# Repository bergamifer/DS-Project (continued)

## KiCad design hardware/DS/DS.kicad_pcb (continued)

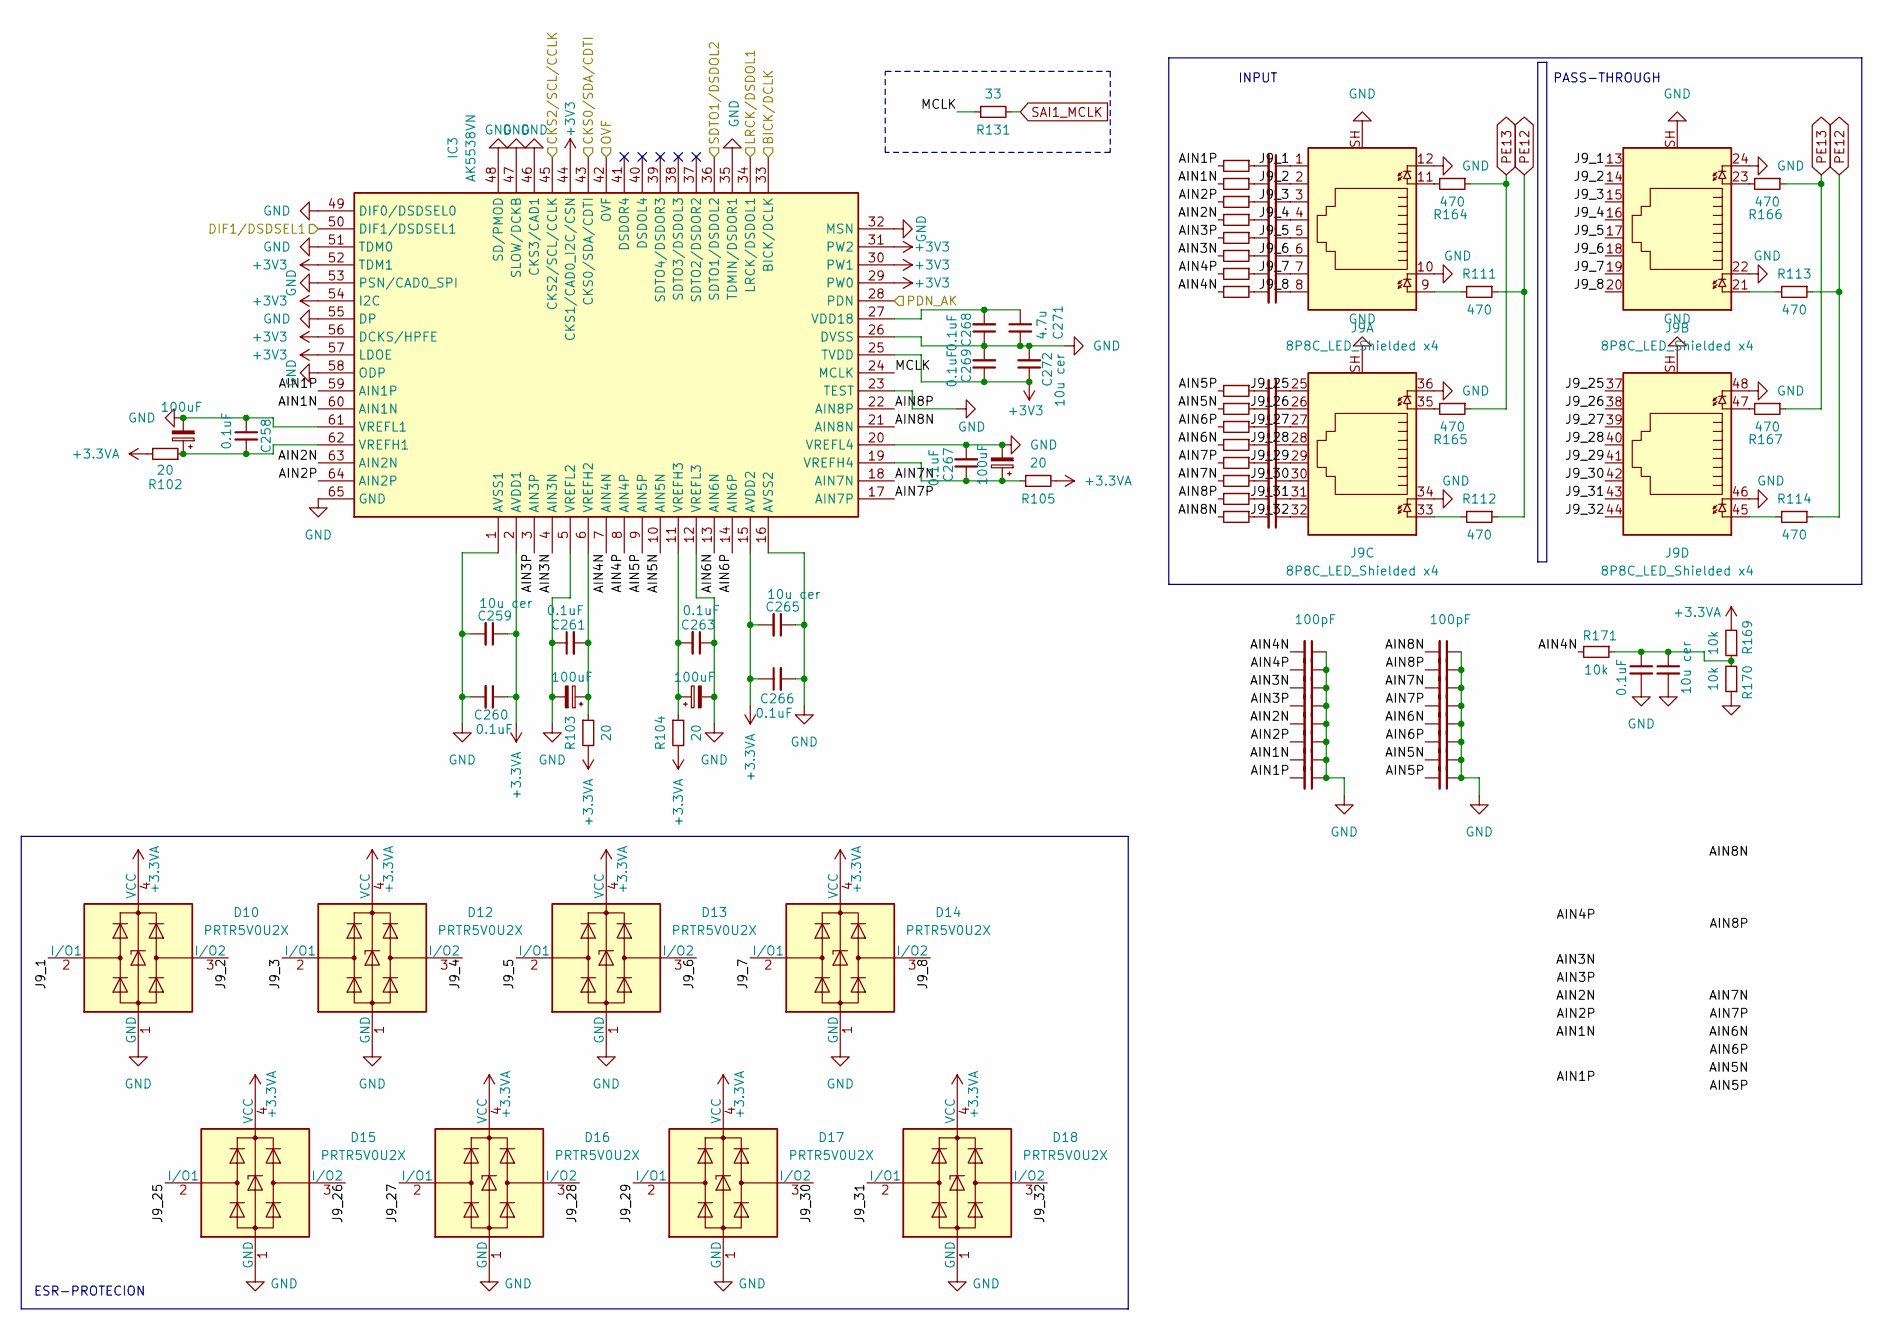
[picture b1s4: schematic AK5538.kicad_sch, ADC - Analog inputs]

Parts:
C58, C258, C260, C261, C263, C266, C267, C268, C269: 0.1uF; C_0402_1005Metric; Mouser part 581-KGM15BR71E104KT
C62, C259, C265, C272: 10u cer; C_0603_1608Metric; Mouser part 187-CL10A106MA8NRWC
C257, C262, C264, C270: 100uF; CP_Elec_5x5.4; Manufacturer_Part_Number RVT1A101M0505; LCSC C18221491
C271: 4.7u; C_0603_1608Metric; Mouser part 581-06036C475KAT2A
C274, C275, C276, C277, C278, C279, C280, C281, C282, C283, C284, C285, C286, C287, C288, C289: 100pF; C_0402_1005Metric; Mouser part TCC0402COG101F500AT
C294, C295, C296, C297, C298, C299, C300, C301, C302, C303, C304, C305, C306, C307, C308, C309: 2.2u; C_0603_1608Metric; Mouser part 187-CL10A225KO8NNNC
D10, D12, D13, D14, D15, D16, D17, D18: PRTR5V0U2X; SOT-143; LCSC C5158049
IC3: AK5538VN; QFN50P900X900X100-65N; Mouser Part Number 412-AK5538VN
J9: 8P8C_LED_Shielded x4; RJ45_Amphenol_RJHSE538X-04; Manufacturer_Part_Number RJ-052-4-2; LCSC C7205134
R102, R103, R104, R105: 20; R_0603_1608Metric; Manufacturer_Part_Number 0603WAF200JT5E; LCSC C22950
R111, R112, R113, R114, R115, R116, R117, R118, R119, R120, R121, R122, R123, R124, R125, R126, R127, R128, R129, R130, R164, R165, R166, R167: 470; R_0402_1005Metric; Manufacturer_Part_Number 0402WGF4700TCE; LCSC C25117
R131: 33; R_0603_1608Metric; Mouser part 71-CRCW060333R0FKEAC
R169, R170, R171: 10k; R_0402_1005Metric; Mouser part 603-RC0603JR-1310KL

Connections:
+3.3VA: C259.1, C260.1, C265.2, C266.1, D10.4 (VCC), D12.4 (VCC), D13.4 (VCC), D14.4 (VCC), D15.4 (VCC), D16.4 (VCC), D17.4 (VCC), D18.4 (VCC), IC3.2 (AVDD1), IC3.15 (AVDD2), R102.2, R103.2, R104.2, R105.2, R169.2; also elsewhere on the board
+3V3: C269.1, C272.1, IC3.25 (TVDD), IC3.29 (PW0), IC3.30 (PW1), IC3.31 (PW2), IC3.44 (CKS1/CAD0_I2C/CSN), IC3.52 (TDM1), IC3.54 (I2C), IC3.56 (DCKS/HPFE), IC3.57 (LDOE); also elsewhere on the board
/ADC_AK5538/AIN1N: C280.2, IC3.60 (AIN1N), R129.2
/ADC_AK5538/AIN1P: C281.2, IC3.59 (AIN1P), R130.2
/ADC_AK5538/AIN2N: C278.2, IC3.63 (AIN2N), R127.2
/ADC_AK5538/AIN2P: C279.2, IC3.64 (AIN2P), R128.2
/ADC_AK5538/AIN3N: C276.2, IC3.4 (AIN3N), R125.2
/ADC_AK5538/AIN3P: C277.2, IC3.3 (AIN3P), R126.2
/ADC_AK5538/AIN4N: C274.2, IC3.7 (AIN4N), R123.2, R171.2
/ADC_AK5538/AIN4P: C275.2, IC3.8 (AIN4P), R124.2
/ADC_AK5538/AIN5N: C288.2, IC3.10 (AIN5N), R121.2
/ADC_AK5538/AIN5P: C289.2, IC3.9 (AIN5P), R122.2
/ADC_AK5538/AIN6N: C286.2, IC3.13 (AIN6N), R119.2
/ADC_AK5538/AIN6P: C287.2, IC3.14 (AIN6P), R120.2
/ADC_AK5538/AIN7N: C284.2, IC3.18 (AIN7N), R117.2
/ADC_AK5538/AIN7P: C285.2, IC3.17 (AIN7P), R118.2
/ADC_AK5538/AIN8N: C282.2, IC3.21 (AIN8N), R115.2
/ADC_AK5538/AIN8P: C283.2, IC3.22 (AIN8P), R116.2
/ADC_AK5538/BICK/DCLK: IC3.33 (BICK/DCLK); also elsewhere on the board
/ADC_AK5538/CKS0/SDA/CDTI: IC3.43 (CKS0/SDA/CDTI); also elsewhere on the board
/ADC_AK5538/CKS2/SCL/CCLK: IC3.45 (CKS2/SCL/CCLK); also elsewhere on the board
/ADC_AK5538/DIF1/DSDSEL1: IC3.50 (DIF1/DSDSEL1); also elsewhere on the board
/ADC_AK5538/J9_1: C309.1, D10.2 (I/O1), J9.1, J9.13
/ADC_AK5538/J9_2: C308.1, D10.3 (I/O2), J9.2, J9.14
/ADC_AK5538/J9_3: C307.1, D12.2 (I/O1), J9.3, J9.15
/ADC_AK5538/J9_4: C306.1, D12.3 (I/O2), J9.4, J9.16
/ADC_AK5538/J9_5: C305.1, D13.2 (I/O1), J9.5, J9.17
/ADC_AK5538/J9_6: C304.1, D13.3 (I/O2), J9.6, J9.18
/ADC_AK5538/J9_7: C303.1, D14.2 (I/O1), J9.7, J9.19
/ADC_AK5538/J9_8: C302.1, D14.3 (I/O2), J9.8, J9.20
/ADC_AK5538/J9_25: C301.1, D15.2 (I/O1), J9.25, J9.37
/ADC_AK5538/J9_26: C300.1, D15.3 (I/O2), J9.26, J9.38
/ADC_AK5538/J9_27: C299.1, D16.2 (I/O1), J9.27, J9.39
/ADC_AK5538/J9_28: C298.1, D16.3 (I/O2), J9.28, J9.40
/ADC_AK5538/J9_29: C297.1, D17.2 (I/O1), J9.29, J9.41
/ADC_AK5538/J9_30: C296.1, D17.3 (I/O2), J9.30, J9.42
/ADC_AK5538/J9_31: C295.1, D18.2 (I/O1), J9.31, J9.43
/ADC_AK5538/J9_32: C294.1, D18.3 (I/O2), J9.32, J9.44
/ADC_AK5538/LRCK/DSDOL1: IC3.34 (LRCK/DSDOL1); also elsewhere on the board
/ADC_AK5538/MCLK: IC3.24 (MCLK), R131.1
/ADC_AK5538/OVF: IC3.42 (OVF); also elsewhere on the board
/ADC_AK5538/PDN_AK: IC3.28 (PDN); also elsewhere on the board
/ADC_AK5538/SDTO1/DSDOL2: IC3.36 (SDTO1/DSDOL2); also elsewhere on the board
GND: C58.2, C62.2, C257.2, C258.1, C259.2, C260.2, C261.1, C262.2, C263.1, C264.2, C265.1, C266.2, C267.2, C268.1, C269.2, C270.2, C271.2, C272.2, C274.1, C275.1, C276.1, C277.1, C278.1, C279.1, C280.1, C281.1, C282.1, C283.1, C284.1, C285.1, C286.1, C287.1, C288.1, C289.1, D10.1 (GND), D12.1 (GND), D13.1 (GND), D14.1 (GND), D15.1 (GND), D16.1 (GND), D17.1 (GND), D18.1 (GND), IC3.1 (AVSS1), IC3.5 (VREFL2), IC3.12 (VREFL3), IC3.16 (AVSS2), IC3.20 (VREFL4), IC3.23 (TEST), IC3.26 (DVSS), IC3.32 (MSN), IC3.35 (TDMIN/DSDOR1), IC3.46 (CKS3/CAD1), IC3.47 (SLOW/DCKB), IC3.48 (SD/PMOD), IC3.49 (DIF0/DSDSEL0), IC3.51 (TDM0), IC3.53 (PSN/CAD0_SPI), IC3.55 (DP), IC3.58 (ODP), IC3.61 (VREFL1), IC3.65 (GND), J9.10, J9.12, J9.22, J9.24, J9.34, J9.36, J9.46, J9.48, J9.SH, R170.1; also elsewhere on the board
unnamed: C58.1, C62.1, R169.1, R170.2, R171.1
unnamed: C294.2, R115.1
unnamed: C295.2, R116.1
unnamed: C296.2, R117.1
unnamed: C297.2, R118.1
unnamed: C298.2, R119.1
unnamed: C299.2, R120.1
unnamed: C300.2, R121.1
unnamed: C301.2, R122.1
unnamed: C302.2, R123.1
unnamed: C303.2, R124.1
unnamed: C304.2, R125.1
unnamed: C305.2, R126.1
unnamed: C306.2, R127.1
unnamed: C307.2, R128.1
unnamed: C308.2, R129.1
unnamed: C309.2, R130.1
unnamed: C268.2, C271.1, IC3.27 (VDD18)
unnamed: C257.1, C258.2, IC3.62 (VREFH1), R102.1
unnamed: C261.2, C262.1, IC3.6 (VREFH2), R103.1
unnamed: C263.2, C264.1, IC3.11 (VREFH3), R104.1
unnamed: C267.1, C270.1, IC3.19 (VREFH4), R105.1
unnamed: J9.9, R111.2
unnamed: J9.11, R164.2
unnamed: J9.21, R113.2
unnamed: J9.23, R166.2
unnamed: J9.33, R112.2
unnamed: J9.35, R165.2
unnamed: J9.45, R114.2
unnamed: J9.47, R167.2
PE12: R111.1, R112.1, R113.1, R114.1; also elsewhere on the board
PE13: R164.1, R165.1, R166.1, R167.1; also elsewhere on the board
SAI1_MCLK: R131.2; also elsewhere on the board

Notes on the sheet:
PASS-THROUGH
INPUT
ESR-PROTECION

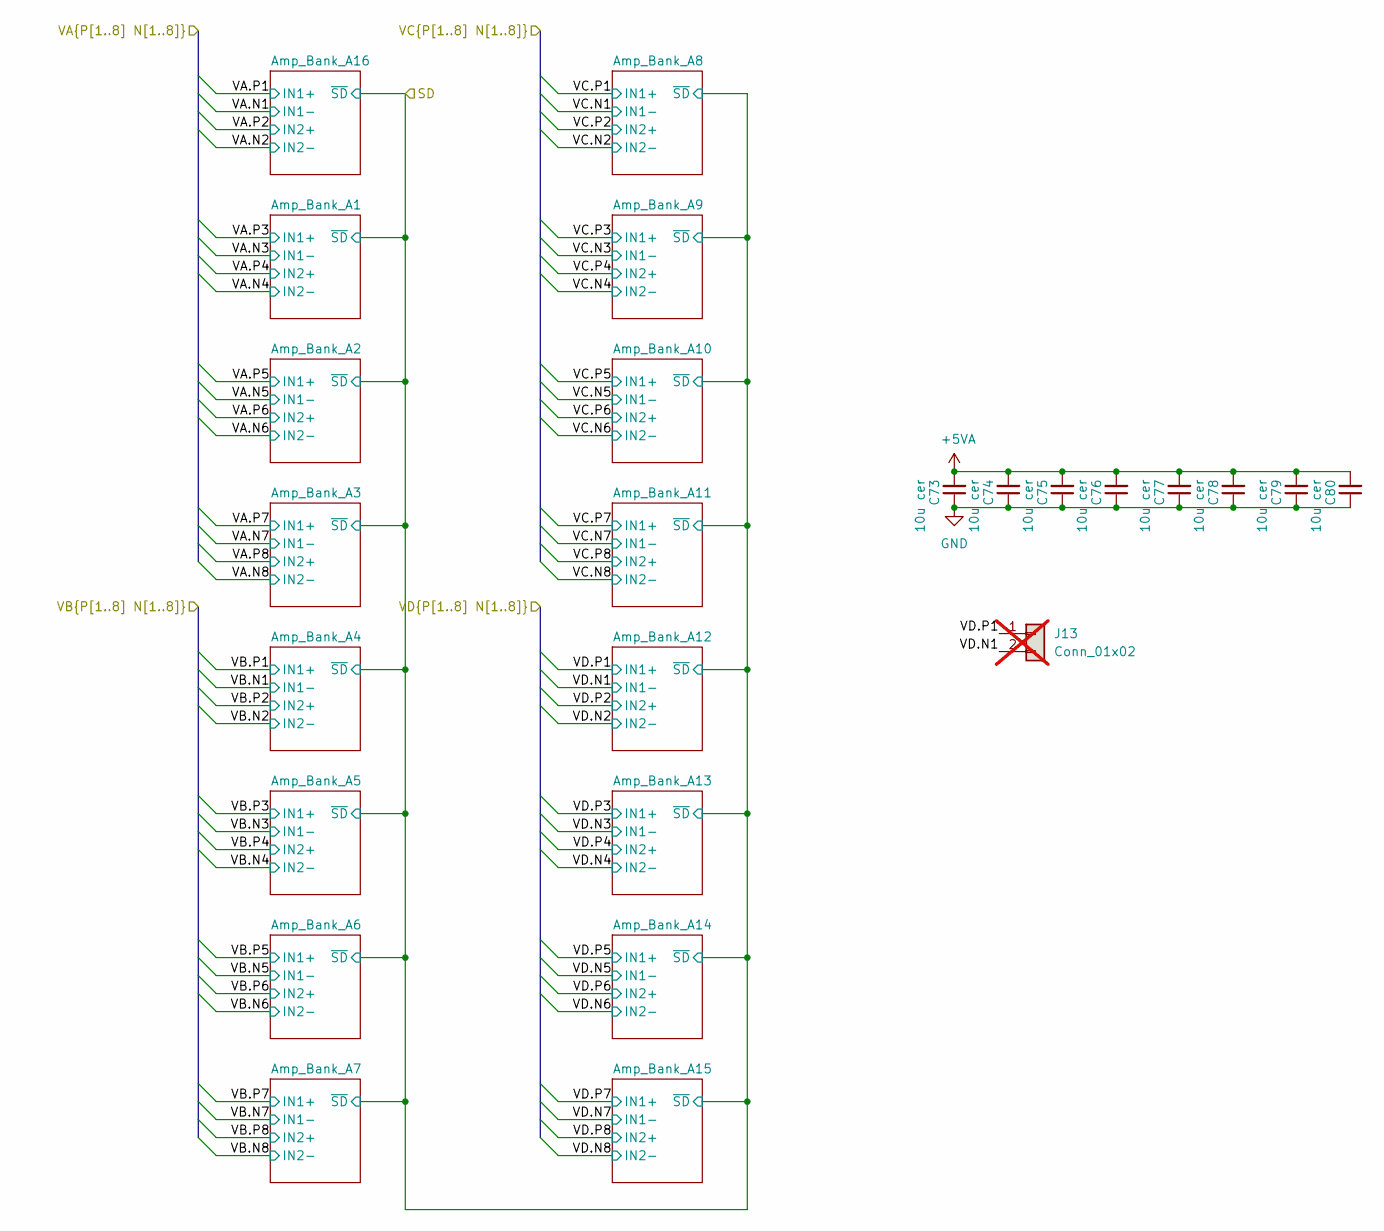
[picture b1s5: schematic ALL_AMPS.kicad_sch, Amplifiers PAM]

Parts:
C73, C74, C75, C76, C77, C78, C79, C80: 10u cer; C_0603_1608Metric; Mouser part 187-CL10A106MA8NRWC
J13: Conn_01x02; PinHeader_1x02_P2.54mm_Vertical; not fitted

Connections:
+5VA: C73.2, C74.2, C75.2, C76.2, C77.2, C78.2, C79.2, C80.2; also elsewhere on the board
/ALL_AMPS/VD.N1: J13.2; also elsewhere on the board
/ALL_AMPS/VD.P1: J13.1; also elsewhere on the board
GND: C73.1, C74.1, C75.1, C76.1, C77.1, C78.1, C79.1, C80.1; also elsewhere on the board

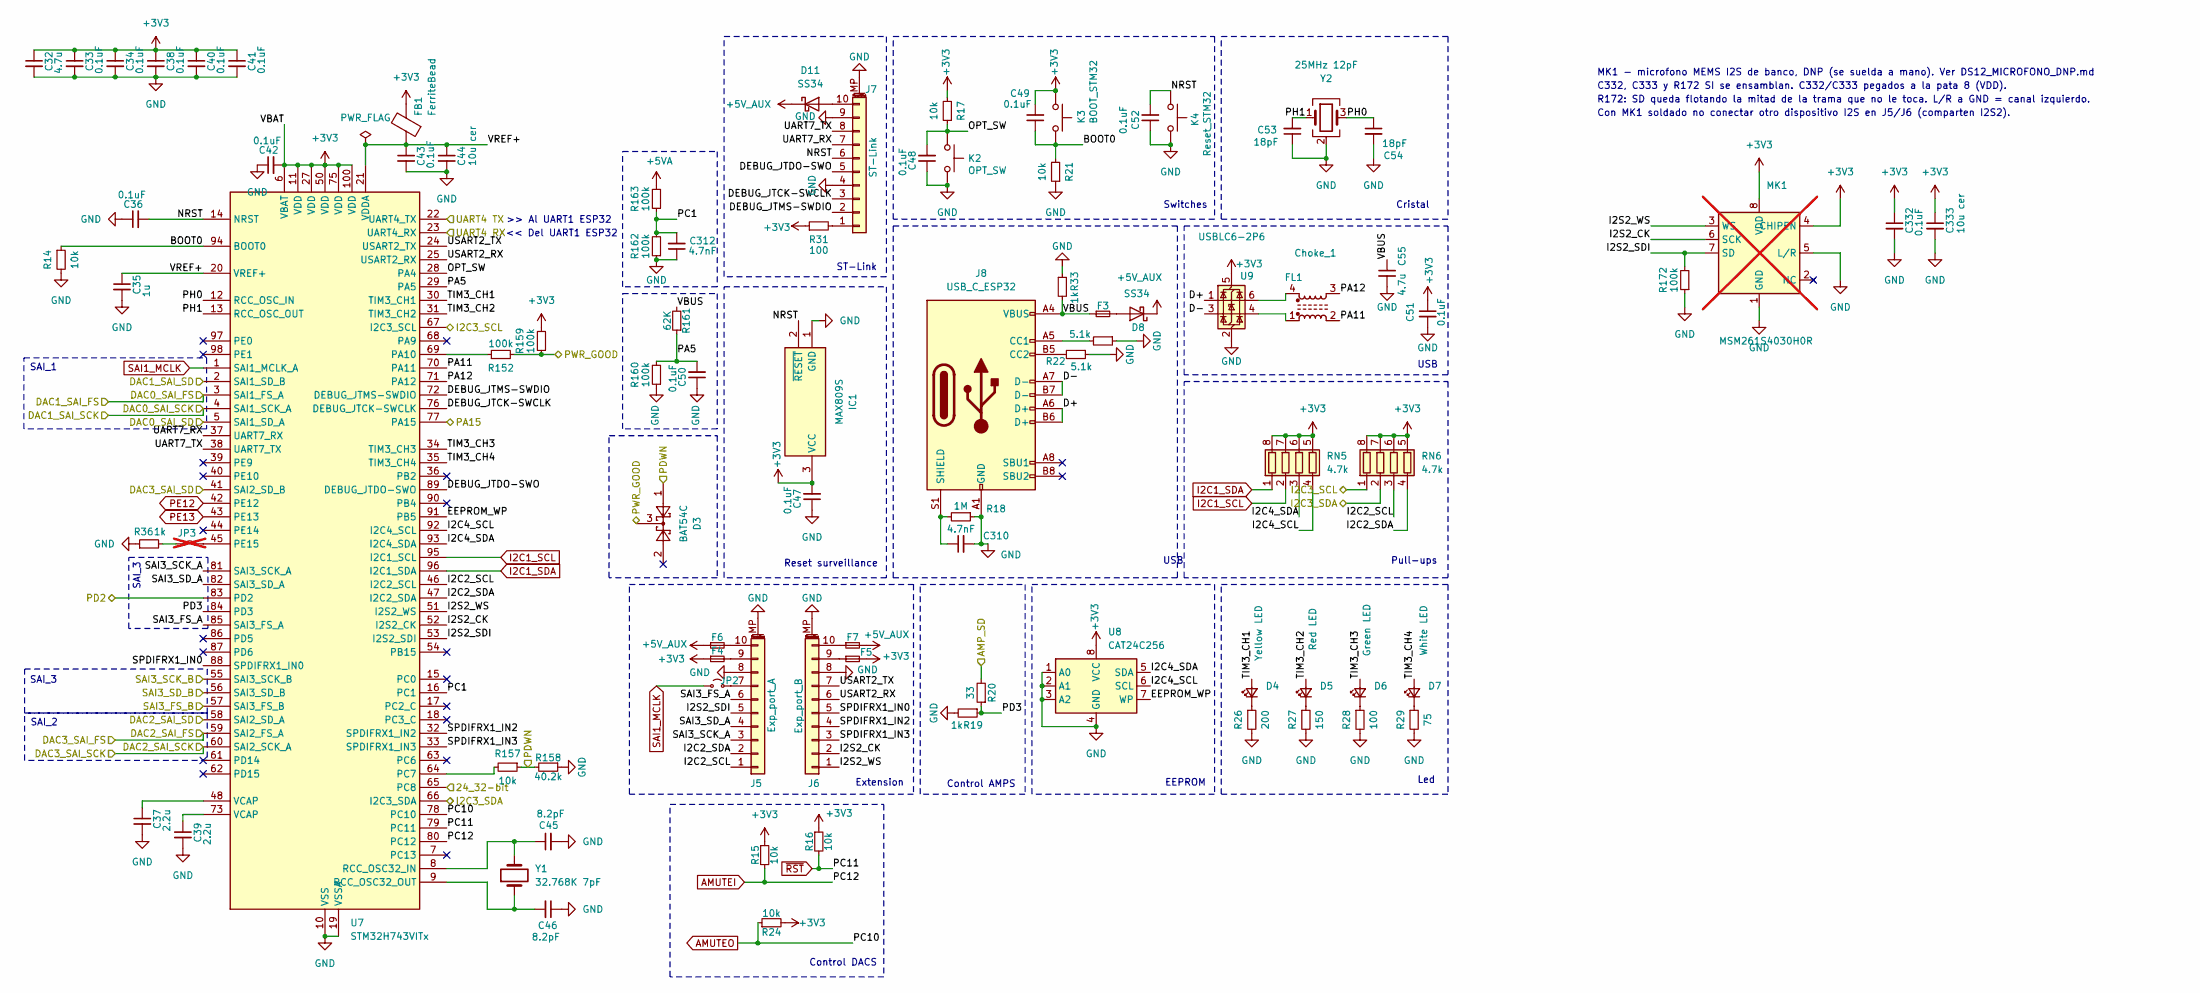
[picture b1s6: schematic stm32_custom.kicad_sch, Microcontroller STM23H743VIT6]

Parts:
C32, C55: 4.7u; C_0603_1608Metric; Mouser part 581-06036C475KAT2A
C33, C34, C36, C38, C40, C41, C42, C43, C47, C48, C49, C50, C51, C52, C332: 0.1uF; C_0402_1005Metric; Mouser part 581-KGM15BR71E104KT
C35: 1u; C_0603_1608Metric; Mouser part 791-0603B105M160CT
C37, C39: 2.2u; C_0603_1608Metric; Mouser part 187-CL10A225KO8NNNC
C44, C333: 10u cer; C_0603_1608Metric; Mouser part 187-CL10A106MA8NRWC
C45, C46: 8.2pF; C_0201_0603Metric; Mouser part 77-VJ0603A120JXQPBC
C53, C54: 18pF; C_0402_1005Metric; Mouser part 80-C0603C100K3G
C310, C312: 4.7nF; C_0603_1608Metric; Manufacturer_Part_Number GCM1885C1H472GA16D; LCSC C2961271
D3: BAT54C; SOT-23; LCSC C2135
D4: Yellow LED; LED_0805_2012Metric; Mouser part 604-APT1608SURCK-AMT
D5: Red LED; LED_0805_2012Metric; Mouser part 604-APT1608CGCK
D6: Green LED; LED_0805_2012Metric; Mouser part 720-BPS2THVG2J8L55S
D7: White LED; LED_0805_2012Metric; Mouser part 327-FKY1111CTR
D8, D11: SS34; D_SMA; Manufacturer_Part_Number SS14HE; LCSC C8678
F3: Fuse_Small; Fuse_1206_3216Metric; Manufacturer_Part_Number SMD1206P110TF/16; LCSC C523825
F4, F5, F6, F7: 500mA; Fuse_1206_3216Metric; Manufacturer_Part_Number BSMD1206-050-30V; LCSC C883126
FB1: FerriteBead; L_0805_2012Metric; Mouser part 81-BLM18DN601SN1D
FL1: Choke_1; L_CommonModeChoke_Murata_DLW21S; Manufacturer_Part_Number DLW21SN900HQ2L; LCSC C97855
IC1: MAX809S; SOT-23-3; Mouser Part Number 700-MAX809TEURT
J5: Exp_port_A; JST_SH_BM10B-SRSS-TB_1x10-1MP_P1.00mm_Vertical; Manufacturer_Part_Number HX 1.0-10P LT; LCSC C5343037
J6: Exp_port_B; JST_SH_BM10B-SRSS-TB_1x10-1MP_P1.00mm_Vertical; Manufacturer_Part_Number HX 1.0-10P LT; LCSC C5343037
J7: ST-Link; JST_SH_BM10B-SRSS-TB_1x10-1MP_P1.00mm_Vertical; Manufacturer_Part_Number HX 1.0-10P LT; LCSC C5343037
J8: USB_C_ESP32; USB_C_Receptacle_G-Switch_GT-USB-7051x; Mouser part 538-217179-0001
JP2: MCLK_EN; SolderJumper-2_P1.3mm_Open_RoundedPad1.0x1.5mm; Manufacturer_Part_Number SMQS-01R-TP; LCSC C5299502
JP3: MCLK_EN; SolderJumper-2_P1.3mm_Bridged2Bar_RoundedPad1.0x1.5mm; not fitted
K2: OPT_SW; SW_SPST_EVQP2_MiddlePushTravel_H2.5mm; Manufacturer_Part_Number TS-1185-W-4P-H1.8-160; LCSC C51927445
K3: BOOT_STM32; SW_SPST_EVQP2_MiddlePushTravel_H2.5mm; Manufacturer_Part_Number TS-1185-W-4P-H1.8-160; LCSC C51927445
K4: Reset_STM32; SW_SPST_EVQP2_MiddlePushTravel_H2.5mm; Manufacturer_Part_Number TS-1185-W-4P-H1.8-160; LCSC C51927445
MK1: MSM261S4030H0R; Manufacturer_Part_Number MSM261S4030H0R; not fitted
R14, R15, R16, R17, R21, R24, R157: 10k; R_0402_1005Metric; Mouser part 603-RC0603JR-1310KL
R18: 1M; R_0603_1608Metric; Mouser part 603-RC0603FR-131ML
R19, R33, R36: 1k; R_0402_1005Metric; Manufacturer_Part_Number CRCW06031K00FKEA; LCSC C11702
R20: 33; R_0603_1608Metric; Mouser part 71-CRCW060333R0FKEAC
R22, R23: 5.1k; R_0603_1608Metric; Mouser part 708-RMCF0603FT5K10
R26: 200; R_0603_1608Metric; Mouser part 594-MCT06030C1200FP5
R27: 150; R_0603_1608Metric; Manufacturer_Part_Number 0603WAF1500T5E; LCSC C22808
R28, R31: 100; R_0603_1608Metric; Manufacturer_Part_Number RCT03100RJLF; LCSC C177347
R29: 75; R_0603_1608Metric; Manufacturer_Part_Number 0603WAF750JT5E; LCSC C4275
R152, R159, R160, R162, R163, R172: 100k; R_0402_1005Metric; LCSC C25741
R158: 40.2k; R_0402_1005Metric; LCSC C2933097
R161: 62K; R_0402_1005Metric; LCSC C37825
RN5, RN6: 4.7k; R_Array_Convex_4x0603; Manufacturer_Part_Number 4D03WGJ0472T5E; LCSC C1980
U7: STM32H743VITx; LQFP-100_14x14mm_P0.5mm; Manufacturer_Part_Number STM32H743VIT6; LCSC C114409
U8: CAT24C256; TSSOP-8_4.4x3mm_P0.65mm; Manufacturer_Part_Number CAT24C256YI-GT3; LCSC C146734
U9: USBLC6-2P6; SOT-666; Manufacturer_Part_Number USBLC6-2P6; LCSC C15999
Y1: 32.768K 7pF; Crystal_SMD_3215-2Pin_3.2x1.5mm; Manufacturer_Part_Number NX3215SA-32.768kHz-EXS00A-MU00202; LCSC C280830
Y2: 25MHz 12pF; Crystal_SMD_3225-4Pin_3.2x2.5mm; Manufacturer_Part_Number X322525MOB4SI; LCSC C9006

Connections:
+3V3: C32.1, C33.1, C34.1, C38.1, C40.1, C41.1, C42.2, C47.2, C49.2, C51.1, C332.1, C333.1, F4.1, F5.2, FB1.2, IC1.3 (VCC), K3.1, MK1.4 (CHIPEN), MK1.8 (VDD), R15.1, R16.1, R17.2, R24.2, R31.1, R159.2, RN5.5 (R4.2), RN5.6 (R3.2), RN5.7 (R2.2), RN5.8 (R1.2), RN6.5 (R4.2), RN6.6 (R3.2), RN6.7 (R2.2), RN6.8 (R1.2), U7.6 (VBAT), U7.11 (VDD), U7.27 (VDD), U7.50 (VDD), U7.75 (VDD), U7.100 (VDD), U8.8 (VCC), U9.5 (VBUS); also elsewhere on the board
+5VA: R163.2; also elsewhere on the board
+5V_AUX: D8.1 (K), D11.1 (K), F6.1, F7.2; also elsewhere on the board
/ADC_AK5538/BICK/DCLK: U7.55 (SAI3_SCK_B); also elsewhere on the board
/ADC_AK5538/CKS0/SDA/CDTI: RN6.2 (R2.1), U7.66 (I2C3_SDA); also elsewhere on the board
/ADC_AK5538/CKS2/SCL/CCLK: RN6.1 (R1.1), U7.67 (I2C3_SCL); also elsewhere on the board
/ADC_AK5538/DIF1/DSDSEL1: U7.65 (PC8); also elsewhere on the board
/ADC_AK5538/LRCK/DSDOL1: U7.57 (SAI3_FS_B); also elsewhere on the board
/ADC_AK5538/OVF: U7.77 (PA15); also elsewhere on the board
/ADC_AK5538/PDN_AK: D3.1, R157.1, R158.2; also elsewhere on the board
/ADC_AK5538/SDTO1/DSDOL2: U7.56 (SAI3_SD_B); also elsewhere on the board
/ALL_AMPS/SD: R20.2; also elsewhere on the board
/DAC0/SAI_FS: U7.3 (SAI1_FS_A); also elsewhere on the board
/DAC0/SAI_SCK: U7.4 (SAI1_SCK_A); also elsewhere on the board
/DAC0/SAI_SD: U7.5 (SAI1_SD_A); also elsewhere on the board
/DAC1/SAI_SD: U7.2 (SAI1_SD_B); also elsewhere on the board
/DAC2/SAI_FS: U7.59 (SAI2_FS_A); also elsewhere on the board
/DAC2/SAI_SCK: U7.60 (SAI2_SCK_A); also elsewhere on the board
/DAC2/SAI_SD: U7.58 (SAI2_SD_A); also elsewhere on the board
/DAC3/SAI_SD: U7.41 (SAI2_SD_B); also elsewhere on the board
/DS_Power/PG: D3.3, R152.2, R159.1; also elsewhere on the board
/esp32-mini/UART1 - RX: U7.22 (UART4_TX); also elsewhere on the board
/esp32-mini/UART1 - TX: U7.23 (UART4_RX); also elsewhere on the board
/stm32_custom/BOOT0: C49.1, K3.2, R14.1, R21.2, U7.94 (BOOT0)
/stm32_custom/D+: J8.A6 (D+), J8.B6 (D+), U9.1 (I/O1)
/stm32_custom/D-: J8.A7 (D-), J8.B7 (D-), U9.3 (I/O2)
/stm32_custom/DEBUG_JTCK-SWCLK: J7.3, U7.76 (DEBUG_JTCK-SWCLK)
/stm32_custom/DEBUG_JTDO-SWO: J7.5, U7.89 (DEBUG_JTDO-SWO)
/stm32_custom/DEBUG_JTMS-SWDIO: J7.2, U7.72 (DEBUG_JTMS-SWDIO)
/stm32_custom/EEPROM_WP: U7.91 (PB5), U8.7 (WP)
/stm32_custom/I2C2_SCL: J5.1, RN6.3 (R3.1), U7.46 (I2C2_SCL)
/stm32_custom/I2C2_SDA: J5.2, RN6.4 (R4.1), U7.47 (I2C2_SDA)
/stm32_custom/I2C4_SCL: RN5.4 (R4.1), U7.92 (I2C4_SCL), U8.6 (SCL)
/stm32_custom/I2C4_SDA: RN5.3 (R3.1), U7.93 (I2C4_SDA), U8.5 (SDA)
/stm32_custom/I2S2_CK: J6.2, MK1.6 (SCK), U7.52 (I2S2_CK)
/stm32_custom/I2S2_SDI: J5.5, MK1.7 (SD), R172.2, U7.53 (I2S2_SDI)
/stm32_custom/I2S2_WS: J6.1, MK1.3 (WS), U7.51 (I2S2_WS)
/stm32_custom/NRST: C36.2, C52.2, IC1.2 (~RESET), J7.6, K4.1, U7.14 (NRST)
/stm32_custom/OPT_SW: C48.2, K2.1, R17.1, U7.28 (PA4)
/stm32_custom/PA5: C50.2, R160.2, R161.1, U7.29 (PA5)
/stm32_custom/PA11: FL1.2, U7.70 (PA11)
/stm32_custom/PA12: FL1.3, U7.71 (PA12)
/stm32_custom/PC1: C312.2, R162.2, R163.1, U7.16 (PC1)
/stm32_custom/PD2: U7.83 (PD2); also elsewhere on the board
/stm32_custom/PD3: R19.1, R20.1, U7.84 (PD3)
/stm32_custom/PH0: C54.1, U7.12 (RCC_OSC_IN), Y2.3
/stm32_custom/PH1: C53.2, U7.13 (RCC_OSC_OUT), Y2.1
/stm32_custom/SAI3_FS_A: J5.6, U7.85 (SAI3_FS_A)
/stm32_custom/SAI3_SCK_A: J5.3, U7.81 (SAI3_SCK_A)
/stm32_custom/SAI3_SD_A: J5.4, U7.82 (SAI3_SD_A)
/stm32_custom/SPDIFRX1_IN0: J6.5, U7.88 (SPDIFRX1_IN0)
/stm32_custom/SPDIFRX1_IN2: J6.4, U7.32 (SPDIFRX1_IN2)
/stm32_custom/SPDIFRX1_IN3: J6.3, U7.33 (SPDIFRX1_IN3)
/stm32_custom/TIM3_CH1: D4.2 (A), U7.30 (TIM3_CH1)
/stm32_custom/TIM3_CH2: D5.2 (A), U7.31 (TIM3_CH2)
/stm32_custom/TIM3_CH3: D6.2 (A), U7.34 (TIM3_CH3)
/stm32_custom/TIM3_CH4: D7.2 (A), U7.35 (TIM3_CH4)
/stm32_custom/UART7_RX: J7.7, U7.37 (UART7_RX)
/stm32_custom/UART7_TX: J7.8, U7.38 (UART7_TX)
/stm32_custom/USART2_RX: J6.6, U7.25 (USART2_RX)
/stm32_custom/USART2_TX: J6.7, U7.24 (USART2_TX)
/stm32_custom/VBUS: C55.1, F3.1, J8.A4 (VBUS), J8.A9 (VBUS), J8.B4 (VBUS), J8.B9 (VBUS), R33.2, R161.2
/stm32_custom/VREF+: C35.1, C43.1, C44.1, FB1.1, U7.20 (VREF+), U7.21 (VDDA)
AMUTEI: R15.2, U7.80 (PC12); also elsewhere on the board
AMUTEO: R24.1, U7.78 (PC10); also elsewhere on the board
GND: C32.2, C33.2, C34.2, C35.2, C36.1, C37.2, C38.2, C39.2, C40.2, C41.2, C42.1, C43.2, C44.2, C45.2, C46.1, C47.1, C48.1, C50.1, C51.2, C52.1, C53.1, C54.2, C55.2, C310.2, C312.1, C332.2, C333.2, IC1.1 (GND), J5.8, J5.MP (MountPin), J6.8, J6.MP (MountPin), J7.4, J7.9, J7.MP (MountPin), J8.A1 (GND), J8.A12 (GND), J8.B1 (GND), J8.B12 (GND), K2.2, K4.2, MK1.1 (GND), MK1.5 (L/R), R14.2, R18.1, R19.2, R21.1, R22.1, R23.1, R26.2, R27.2, R28.2, R29.2, R33.1, R36.1, R158.1, R160.1, R162.1, R172.1, U7.10 (VSS), U7.19 (VSSA), U7.26 (VSS), U7.49 (VSS), U7.74 (VSS), U7.99 (VSS), U8.1 (A0), U8.2 (A1), U8.3 (A2), U8.4 (GND), U9.2 (GND), Y2.2 (G), Y2.4 (G); also elsewhere on the board
I2C1_SCL: RN5.2 (R2.1), U7.95 (I2C1_SCL); also elsewhere on the board
I2C1_SDA: RN5.1 (R1.1), U7.96 (I2C1_SDA); also elsewhere on the board
unnamed: C37.1, U7.48 (VCAP)
unnamed: C39.1, U7.73 (VCAP)
unnamed: D4.1 (K), R26.1
unnamed: D5.1 (K), R27.1
unnamed: D6.1 (K), R28.1
unnamed: D7.1 (K), R29.1
unnamed: D8.2 (A), F3.2
unnamed: D11.2 (A), J7.10
unnamed: FL1.1, U9.4 (I/O2)
unnamed: FL1.4, U9.6 (I/O1)
unnamed: J5.7, JP2.2 (B)
unnamed: F4.2, J5.9
unnamed: F6.2, J5.10
unnamed: F5.1, J6.9
unnamed: F7.1, J6.10
unnamed: J7.1, R31.2
unnamed: J8.A5 (CC1), R23.2
unnamed: J8.B5 (CC2), R22.2
unnamed: C310.1, J8.S1 (SHIELD), R18.2
unnamed: JP3.1 (A), R36.2
unnamed: JP3.2 (B), U7.45 (PE15)
unnamed: R152.1, U7.69 (PA10)
unnamed: R157.2, U7.64 (PC7)
unnamed: C45.1, U7.8 (RCC_OSC32_IN), Y1.2
unnamed: C46.2, U7.9 (RCC_OSC32_OUT), Y1.1
PE12: U7.42 (PE12); also elsewhere on the board
PE13: U7.43 (PE13); also elsewhere on the board
SAI1_MCLK: JP2.1 (A), U7.1 (SAI1_MCLK_A); also elsewhere on the board
~RST: R16.2, U7.79 (PC11); also elsewhere on the board

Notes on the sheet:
ST-Link
SAI_1
Switches
SAI_3
Control AMPS
USB
<< Del UART1 ESP32
Cristal
>> Al UART1 ESP32
SAI_2
Reset surveillance
Extension
EEPROM
Control DACS
Pull-ups
Led
MK1 - microfono MEMS I2S de banco, DNP (se suelda a mano). Ver DS12_MICROFONO_DNP.md
C332, C333 y R172 SI se ensamblan. C332/C333 pegados a la pata 8 (VDD).
R172: SD queda flotando la mitad de la trama que no le toca. L/R a GND = canal izquierdo.
Con MK1 soldado no conectar otro dispositivo I2S en J5/J6 (comparten I2S2).

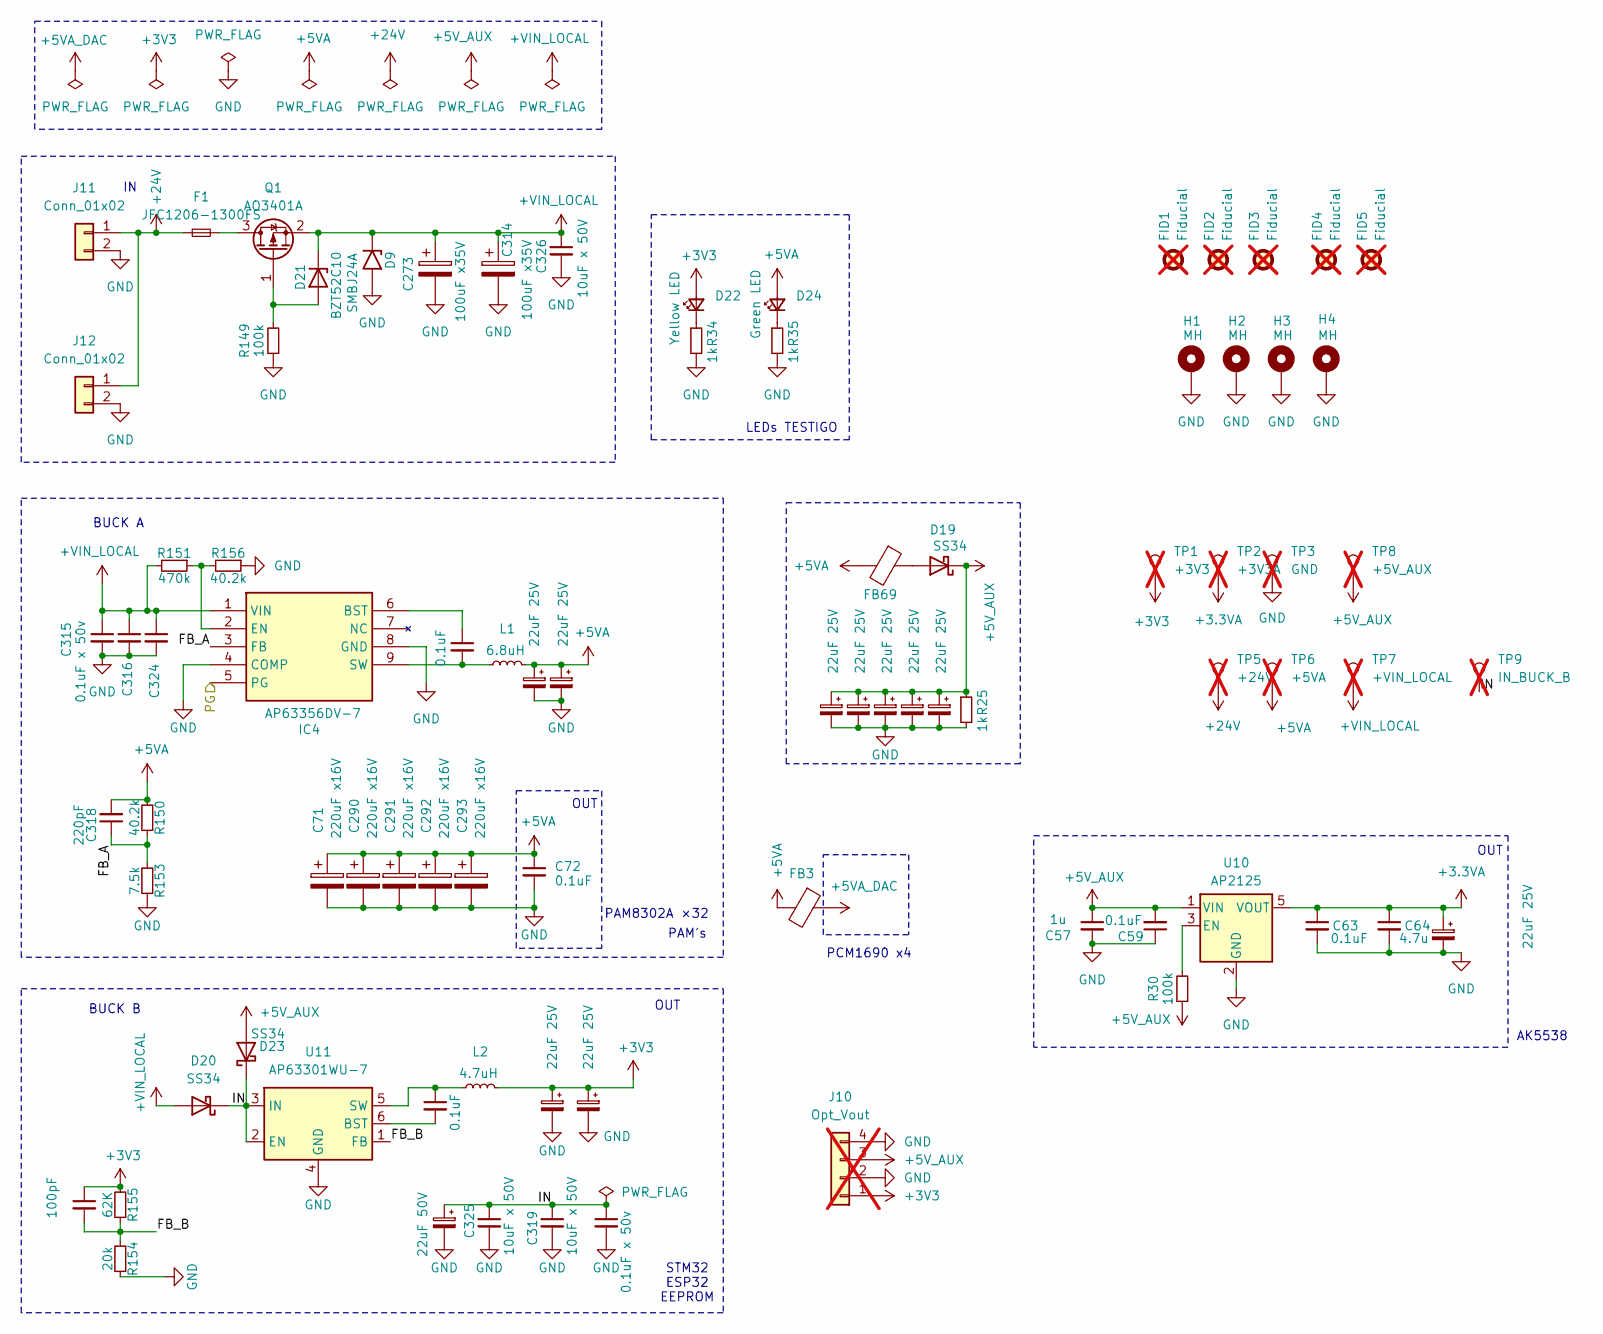
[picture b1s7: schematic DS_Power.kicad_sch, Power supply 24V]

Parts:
C57: 1u; C_0603_1608Metric; Mouser part 791-0603B105M160CT
C59, C61, C63, C72, C317: 0.1uF; C_0402_1005Metric; Mouser part 581-KGM15BR71E104KT
C60: 22uF 50V; CP_Elec_6.3x5.4; Manufacturer_Part_Number RVT1H220M0605; LCSC C72505
C64: 4.7u; C_0603_1608Metric; Mouser part 581-06036C475KAT2A
C67, C69, C70, C313, C321, C322, C327, C328, C330, C331: 22uF 25V; C_0805_2012Metric; Manufacturer_Part_Number CL21A226MAQNNNE; LCSC C45783
C71, C290, C291, C292, C293: 220uF x16V; CP_Elec_6.3x7.7; LCSC C25503905
C273, C314: 100uF x35V; CP_Elec_6.3x7.7; LCSC C2836437
C315, C320: 0.1uF x 50v; C_0603_1608Metric; Mouser part 581-KGM15BR71E104KT
C316, C319, C324, C325, C326: 10uF x 50V; C_1210_3225Metric; LCSC C138687
C318: 220pF; C_0402_1005Metric; Mouser part 581-KGM15BR71E104KT
C323: 100pF; C_0402_1005Metric; Mouser part TCC0402COG101F500AT
D9: SMBJ24A; D_SMB; Manufacturer_Part_Number SMBJ24A; LCSC C908801
D19: SS34; D_SMA; Manufacturer_Part_Number SS14HE; LCSC C8678
D20, D23: SS34; D_SMA; LCSC C8678
D21: BZT52C10; D_SOD-123F; LCSC C173431
D22: Yellow LED; LED_0805_2012Metric; Mouser part 604-APT1608SURCK-AMT
D24: Green LED; LED_0805_2012Metric; Mouser part 720-BPS2THVG2J8L55S
F1: JFC1206-1300FS; Fuse_1206_3216Metric; Manufacturer_Part_Number SMD1206P110TF/16; LCSC C136347
FB3: FerriteBead; L_0805_2012Metric; Mouser part CBW201209U601T
FB69: FerriteBead; L_0805_2012Metric; Mouser part 81-BLM18DN601SN1D
FID1, FID2, FID3: Fiducial; Fiducial_1mm_Mask3mm; not fitted
FID4, FID5: Fiducial; Fiducial_0.5mm_Mask1mm; not fitted
H1, H2, H3, H4: MH; MountingHole_2.7mm_Pad_Via
IC4: AP63356DV-7; AP63356DV7; Mouser Part Number 621-AP63356DV-7
J10: Opt_Vout; JST_XH_B4B-XH-A_1x04_P2.50mm_Vertical; Manufacturer_Part_Number B4B-XH-A; not fitted
J11, J12: Conn_01x02; PhoenixContact_MSTBVA_2,5_2-G-5,08_1x02_P5.08mm_Vertical; LCSC C41784016
L1: 6.8uH; L_Sunlord_MWSA1004S; LCSC C408485
L2: 4.7uH; L_Sunlord_MWSA0603S; LCSC C408447
Q1: AO3401A; SOT-23; LCSC C15127
R25, R34, R35: 1k; R_0402_1005Metric; Manufacturer_Part_Number CRCW06031K00FKEA; LCSC C11702
R30, R149: 100k; R_0402_1005Metric; LCSC C25741
R150, R156: 40.2k; R_0402_1005Metric; LCSC C2933097
R151: 470k; R_0603_1608Metric; LCSC C23178
R153: 7.5k; R_0603_1608Metric; LCSC C23234
R154: 20k; R_0402_1005Metric; LCSC C25765
R155: 62K; R_0402_1005Metric; LCSC C37825
TP1: +3V3; TestPoint_Pad_D1.5mm; not fitted
TP2: +3V3A; TestPoint_Pad_D1.5mm; not fitted
TP3: GND; TestPoint_Pad_D1.5mm; not fitted
TP5: +24V; TestPoint_Pad_D1.5mm; not fitted
TP6: +5VA; TestPoint_Pad_D1.5mm; not fitted
TP7: +VIN_LOCAL; TestPoint_Pad_D1.5mm; not fitted
TP8: +5V_AUX; TestPoint_Pad_D1.5mm; not fitted
TP9: IN_BUCK_B; TestPoint_Pad_D1.5mm; not fitted
U10: AP2125; SOT-23-5; LCSC C110463
U11: AP63301WU-7; TSOT-23-6; LCSC C2158003

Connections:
+3.3VA: C63.1, C64.1, C67.1, TP2.1 (1_1), U10.5 (VOUT); also elsewhere on the board
+3V3: C321.1, C322.1, C323.1, D22.2 (A), J10.1, L2.2, R155.2, TP1.1 (1_1); also elsewhere on the board
+5VA: C69.1, C70.1, C71.1, C72.1, C290.1, C291.1, C292.1, C293.1, C318.2, D24.2 (A), FB3.2, FB69.2, L1.2, R150.2, TP6.1 (1_1); also elsewhere on the board
+5VA_DAC: FB3.1; also elsewhere on the board
+5V_AUX: C57.1, C59.2, C313.1, C327.1, C328.1, C330.1, C331.1, D19.1 (K), D23.2 (A), J10.3, R25.1, R30.1, TP8.1 (1_1), U10.1 (VIN); also elsewhere on the board
+24V: F1.1, J11.1, J12.1, TP5.1 (1_1)
+VIN_LOCAL: C273.1, C314.1, C315.1, C316.1, C324.1, C326.1, D9.1 (A1), D20.2 (A), D21.1 (K), IC4.1 (VIN), Q1.2 (S), R151.2, TP7.1 (1_1)
/DS_Power/FB_A: C318.1, IC4.3 (FB), R150.1, R153.2
/DS_Power/FB_B: C323.2, R154.2, R155.1, U11.1 (FB)
/DS_Power/IN: C60.1, C319.1, C320.1, C325.1, D20.1 (K), D23.1 (K), TP9.1 (1_1), U11.2 (EN), U11.3 (IN)
/DS_Power/PG: IC4.5 (PG); also elsewhere on the board
GND: C57.2, C59.1, C60.2, C63.2, C64.2, C67.2, C69.2, C70.2, C71.2, C72.2, C273.2, C290.2, C291.2, C292.2, C293.2, C313.2, C314.2, C315.2, C316.2, C319.2, C320.2, C321.2, C322.2, C324.2, C325.2, C326.2, C327.2, C328.2, C330.2, C331.2, D9.2 (A2), H1.1 (1_1), H2.1 (1_1), H3.1 (1_1), H4.1 (1_1), IC4.4 (COMP), IC4.8 (GND), J10.2, J10.4, J11.2, J12.2, R25.2, R34.2, R35.2, R149.1, R153.1, R154.1, R156.1, TP3.1 (1_1), U10.2 (GND), U11.4 (GND); also elsewhere on the board
unnamed: D19.2 (A), FB69.1
unnamed: D21.2 (A), Q1.1 (G), R149.2
unnamed: D22.1 (K), R34.1
unnamed: D24.1 (K), R35.1
unnamed: C317.1, IC4.6 (BST)
unnamed: IC4.2 (EN), R151.1, R156.2
unnamed: C317.2, IC4.9 (SW), L1.1
unnamed: F1.2, Q1.3 (D)
unnamed: R30.2, U10.3 (EN)
unnamed: C61.2, U11.6 (BST)
unnamed: C61.1, L2.1, U11.5 (SW)

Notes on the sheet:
PAM8302A ×32
PAM's
BUCK A
LEDs TESTIGO
PCM1690 x4
AK5538
OUT
STM32 ESP32 EEPROM
BUCK B
